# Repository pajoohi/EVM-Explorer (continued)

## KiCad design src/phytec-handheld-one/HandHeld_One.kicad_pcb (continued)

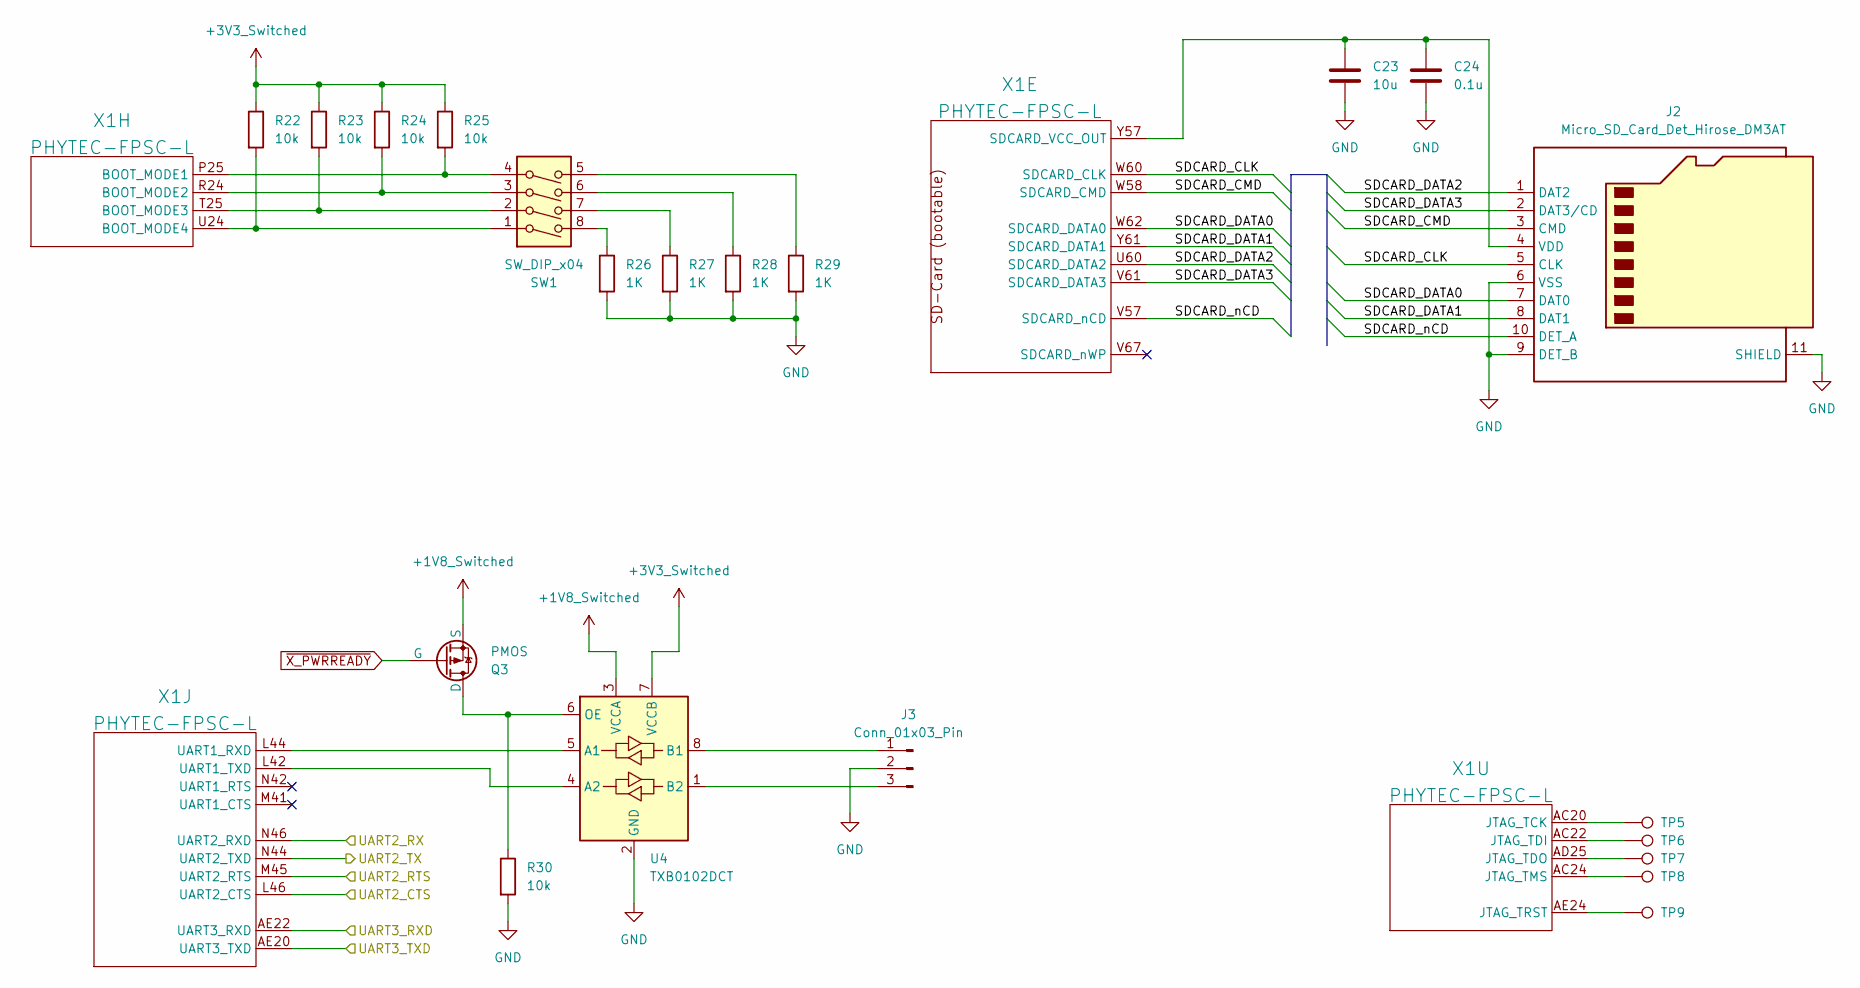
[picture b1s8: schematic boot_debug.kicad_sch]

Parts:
C23: 10u; C_0402_1005Metric_Pad0.74x0.62mm_HandSolder
C24: 0.1u; C_0402_1005Metric_Pad0.74x0.62mm_HandSolder
J2: Micro_SD_Card_Det_Hirose_DM3AT; microSD_HC_Hirose_DM3BT-DSF-PEJS
J3: Conn_01x03_Pin; PinHeader_1x03_P2.54mm_Vertical
Q3: PMOS; SC-59_Handsoldering
R22, R23, R24, R25, R30: 10k; R_0402_1005Metric_Pad0.72x0.64mm_HandSolder
R26, R27, R28, R29: 1K; R_0402_1005Metric_Pad0.72x0.64mm_HandSolder
SW1: SW_DIP_x04; SW_DIP_SPSTx04_Slide_Copal_CHS-04B_W7.62mm_P1.27mm
TP5, TP6, TP7, TP8, TP9: TestPoint; TestPoint_Pad_D1.0mm
U4: TXB0102DCT; TSSOP-8_3x3mm_P0.65mm
X1: PHYTEC-FPSC-L; PHYTEC-FPSC-BASIS-L-Socket

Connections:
+1V8_Switched: Q3.2 (S), U4.3 (VCCA); also elsewhere on the board
+3V3_Switched: R22.1, R23.1, R24.1, R25.1, U4.7 (VCCB); also elsewhere on the board
/Boot and Debug/SDCARD_CLK: J2.5 (CLK), X1.W60 (SDCARD_CLK)
/Boot and Debug/SDCARD_CMD: J2.3 (CMD), X1.W58 (SDCARD_CMD)
/Boot and Debug/SDCARD_DATA0: J2.7 (DAT0), X1.W62 (SDCARD_DATA0)
/Boot and Debug/SDCARD_DATA1: J2.8 (DAT1), X1.Y61 (SDCARD_DATA1)
/Boot and Debug/SDCARD_DATA2: J2.1 (DAT2), X1.U60 (SDCARD_DATA2)
/Boot and Debug/SDCARD_DATA3: J2.2 (DAT3/CD), X1.V61 (SDCARD_DATA3)
/Boot and Debug/SDCARD_nCD: J2.10 (DET_A), X1.V57 (SDCARD_nCD)
/Boot and Debug/UART2_CTS: X1.L46 (UART2_CTS); also elsewhere on the board
/Boot and Debug/UART2_RTS: X1.M45 (UART2_RTS); also elsewhere on the board
/Boot and Debug/UART2_RX: X1.N46 (UART2_RXD); also elsewhere on the board
/Boot and Debug/UART2_TX: X1.N44 (UART2_TXD); also elsewhere on the board
/Boot and Debug/UART3_RXD: X1.AE22 (UART3_RXD)
/Boot and Debug/UART3_TXD: X1.AE20 (UART3_TXD)
GND: C23.2, C24.2, J2.6 (VSS), J2.9 (DET_B), J2.11 (SHIELD), J3.2, R26.2, R27.2, R28.2, R29.2, R30.2, U4.2 (GND); also elsewhere on the board
unnamed: C23.1, C24.1, J2.4 (VDD), X1.Y57 (SDCARD_VCC_OUT)
unnamed: J3.1, U4.8 (B1)
unnamed: J3.3, U4.1 (B2)
unnamed: Q3.3 (D), R30.1, U4.6 (OE)
unnamed: R26.1, SW1.8
unnamed: R27.1, SW1.7
unnamed: R28.1, SW1.6
unnamed: R29.1, SW1.5
unnamed: U4.5 (A1), X1.L44 (UART1_RXD)
unnamed: U4.4 (A2), X1.L42 (UART1_TXD)
unnamed: R25.2, SW1.4, X1.P25 (BOOT_MODE1)
unnamed: R24.2, SW1.3, X1.R24 (BOOT_MODE2)
unnamed: R23.2, SW1.2, X1.T25 (BOOT_MODE3)
unnamed: R22.2, SW1.1, X1.U24 (BOOT_MODE4)
unnamed: TP5.1, X1.AC20 (JTAG_TCK)
unnamed: TP6.1, X1.AC22 (JTAG_TDI)
unnamed: TP7.1, X1.AD25 (JTAG_TDO)
unnamed: TP8.1, X1.AC24 (JTAG_TMS)
unnamed: TP9.1, X1.AE24 (JTAG_TRST)
~X_PWRREADY: Q3.1 (G); also elsewhere on the board

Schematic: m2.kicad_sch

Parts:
C51, C53: 1u; C_0402_1005Metric_Pad0.74x0.62mm_HandSolder
C52, C54: 0.1u; C_0402_1005Metric_Pad0.74x0.62mm_HandSolder
J6: Bus_M.2_Socket_E; JAE_SM3ZS067U310AER1200
MP1: M2 x 1.5mm; WA-SMSI_9774015243; PART-NUMBER 9774015243R
Q4: PMOS; SC-59_Handsoldering
X1: PHYTEC-FPSC-L; PHYTEC-FPSC-BASIS-L-Socket
XTAL1: OM-7604-C7-32.768KHZ-20PPM-TA-QC; OM-7604-C7_MCX

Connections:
+3V3_Switched: C51.1, C52.1, C53.1, C54.1, J6.2 (3.3V), J6.4 (3.3V), J6.72 (3.3V), J6.74 (3.3V), XTAL1.3 (CLKOE), XTAL1.4 (VDD); also elsewhere on the board
+5V: Q4.2 (S); also elsewhere on the board
/Boot and Debug/UART2_CTS: J6.34 (UART_CTS); also elsewhere on the board
/Boot and Debug/UART2_RTS: J6.36 (UART_RTS); also elsewhere on the board
/Boot and Debug/UART2_RX: J6.22 (UART_RXD); also elsewhere on the board
/Boot and Debug/UART2_TX: J6.32 (UART_TXD); also elsewhere on the board
/Display/TP_I2C_SCL: J6.60 (I2C_CLK); also elsewhere on the board
/Display/TP_I2C_SDA: J6.58 (I2C_DATA); also elsewhere on the board
/IO/GPIO1: J6.62 (~ALERT); also elsewhere on the board
/IO/GPIO4: J6.21 (~SDIO_WAKE); also elsewhere on the board
/M.2/USB2_D+: J6.3 (USB_D+), X1.AA62 (USB2_D_P)
/M.2/USB2_D-: J6.5 (USB_D-), X1.AB61 (USB2_D_N)
/M.2/~M.2_UART_Wake: J6.20 (~UART_WAKE)
GND: C51.2, C52.2, C53.2, C54.2, J6.1 (GND), J6.7 (GND), J6.18 (GND), J6.33 (GND), J6.39 (GND), J6.45 (GND), J6.51 (GND), J6.57 (GND), J6.63 (GND), J6.69 (GND), J6.75 (GND), J6.S1, J6.S2, MP1.1, XTAL1.2 (GND); also elsewhere on the board
unnamed: J6.9 (SDIO_CLK), X1.H57 (SDIO_CLK)
unnamed: J6.11 (SDIO_CMD), X1.G56 (SDIO_CMD)
unnamed: J6.13 (SDIO_DATA0), X1.G62 (SDIO_DATA0)
unnamed: J6.15 (SDIO_DATA1), X1.H61 (SDIO_DATA1)
unnamed: J6.17 (SDIO_DATA2), X1.G60 (SDIO_DATA2)
unnamed: J6.19 (SDIO_DATA3), X1.G58 (SDIO_DATA3)
unnamed: J6.50 (SUSCLK), XTAL1.1 (CLKOUT)
unnamed: Q4.3 (D), X1.AA58 (USB2_VBUS)
~X_PWRREADY: Q4.1 (G); also elsewhere on the board

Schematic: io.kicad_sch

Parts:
C49, C50: 0.1u; C_0402_1005Metric_Pad0.74x0.62mm_HandSolder
R39, R40, R41, R42, R43, R44: 2k; R_0402_1005Metric_Pad0.72x0.64mm_HandSolder
U8: ADXL343; LGA-14_3x5mm_P0.8mm_LayoutBorder1x6y
X1: PHYTEC-FPSC-L; PHYTEC-FPSC-BASIS-L-Socket

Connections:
+1V8_Switched: C50.1, R39.1, R40.1, R41.1, R42.1, R43.1, R44.1, U8.1 (Vdd_I/O); also elsewhere on the board
+3V3_Switched: C49.1, U8.6 (Vs); also elsewhere on the board
/Audio/Audio_I2C_SCL: R40.2, X1.L60 (I2C2_SCL); also elsewhere on the board
/Audio/Audio_I2C_SDA: R39.2, X1.L58 (I2C2_SDA); also elsewhere on the board
/Display/LCD_BKLT_PWM: X1.AN52 (PWM4); also elsewhere on the board
/Display/LCD_PWM: X1.AL42 (PWM3); also elsewhere on the board
/Display/TP_I2C_SCL: R42.2, X1.M61 (I2C3_SCL); also elsewhere on the board
/Display/TP_I2C_SDA: R41.2, X1.N60 (I2C3_SDA); also elsewhere on the board
/Display/TP_INT: X1.AL32 (GPIO3); also elsewhere on the board
/Display/TP_RST: X1.AN30 (GPIO5); also elsewhere on the board
/IO/GPIO1: X1.N40 (GPIO1); also elsewhere on the board
/IO/GPIO4: X1.AL34 (GPIO4); also elsewhere on the board
/IO/GPIO6: X1.AN32 (GPIO6); also elsewhere on the board
/IO/GPIO7: X1.AN34 (GPIO7); also elsewhere on the board
/IO/I2C4_SCL: R44.2, X1.AN40 (I2C5_SCL/I3C_SCL); also elsewhere on the board
/IO/I2C4_SDA: R43.2, X1.AN42 (I2C5_SDA/I3C_SDA); also elsewhere on the board
/IO/SPI1.MISO: U8.12 (SDO/ADDR), X1.N34 (SPI1_MISO)
/IO/SPI1.MOSI: U8.13 (SDA/SDI/SDIO), X1.N32 (SPI1_MOSI)
/IO/SPI1.SCLK: U8.14 (SCL/SCLK), X1.M33 (SPI1_SCLK)
/IO/SPI1.~CS: U8.7 (~CS), X1.L34 (SPI1_nCS)
GND: C49.2, C50.2, U8.2 (GND), U8.4 (GND), U8.5 (GND); also elsewhere on the board
unnamed: U8.8 (INT1), X1.L40 (GPIO2)

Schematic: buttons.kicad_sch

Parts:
R47: 10k; R_0402_1005Metric_Pad0.72x0.64mm_HandSolder
SW2: SW_Push; SW_EVP-ASAC1A

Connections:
+1V8_Switched: R47.1; also elsewhere on the board
/Micro Controller/Button/button: R47.2, SW2.1; also elsewhere on the board
GND: SW2.2; also elsewhere on the board

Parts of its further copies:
R48, R49, R50, R51, R52, R53, R54, R55, R56, R57: 10k; R_0402_1005Metric_Pad0.72x0.64mm_HandSolder
SW3, SW4, SW5, SW6, SW7, SW8, SW9, SW10, SW11, SW12: SW_Push; SW_EVP-ASAC1A

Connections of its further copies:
+1V8_Switched: R48.1, R49.1, R50.1, R51.1, R52.1, R53.1, R54.1, R55.1, R56.1, R57.1; also elsewhere on the board
/Micro Controller/Button1/button: R48.2, SW3.1; also elsewhere on the board
/Micro Controller/Button2/button: R49.2, SW4.1; also elsewhere on the board
/Micro Controller/Button3/button: R50.2, SW5.1; also elsewhere on the board
/Micro Controller/Button4/button: R51.2, SW6.1; also elsewhere on the board
/Micro Controller/Button5/button: R52.2, SW7.1; also elsewhere on the board
/Micro Controller/Button6/button: R53.2, SW8.1; also elsewhere on the board
/Micro Controller/Button7/button: R54.2, SW9.1; also elsewhere on the board
/Micro Controller/Button8/button: R55.2, SW10.1; also elsewhere on the board
/Micro Controller/Button9/button: R56.2, SW11.1; also elsewhere on the board
/Micro Controller/Button10/button: R57.2, SW12.1; also elsewhere on the board
GND: SW3.2, SW4.2, SW5.2, SW6.2, SW7.2, SW8.2, SW9.2, SW10.2, SW11.2, SW12.2; also elsewhere on the board

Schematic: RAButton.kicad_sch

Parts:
R60: 10k; R_0402_1005Metric_Pad0.72x0.64mm_HandSolder
SW15: SW_Push_Shielded; SW_EVQ-P46B3M

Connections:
+1V8_Switched: R60.1; also elsewhere on the board
/Micro Controller/Right Angle Button1/button: R60.2, SW15.1; also elsewhere on the board
GND: SW15.2, SW15.3 (B), SW15.4 (B); also elsewhere on the board

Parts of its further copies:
R58: 10k; R_0402_1005Metric_Pad0.72x0.64mm_HandSolder
SW13: SW_Push_Shielded; SW_EVQ-P46B3M

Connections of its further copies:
+1V8_Switched: R58.1; also elsewhere on the board
/Micro Controller/Right Angle Button/button: R58.2, SW13.1; also elsewhere on the board
GND: SW13.2, SW13.3 (B), SW13.4 (B); also elsewhere on the board

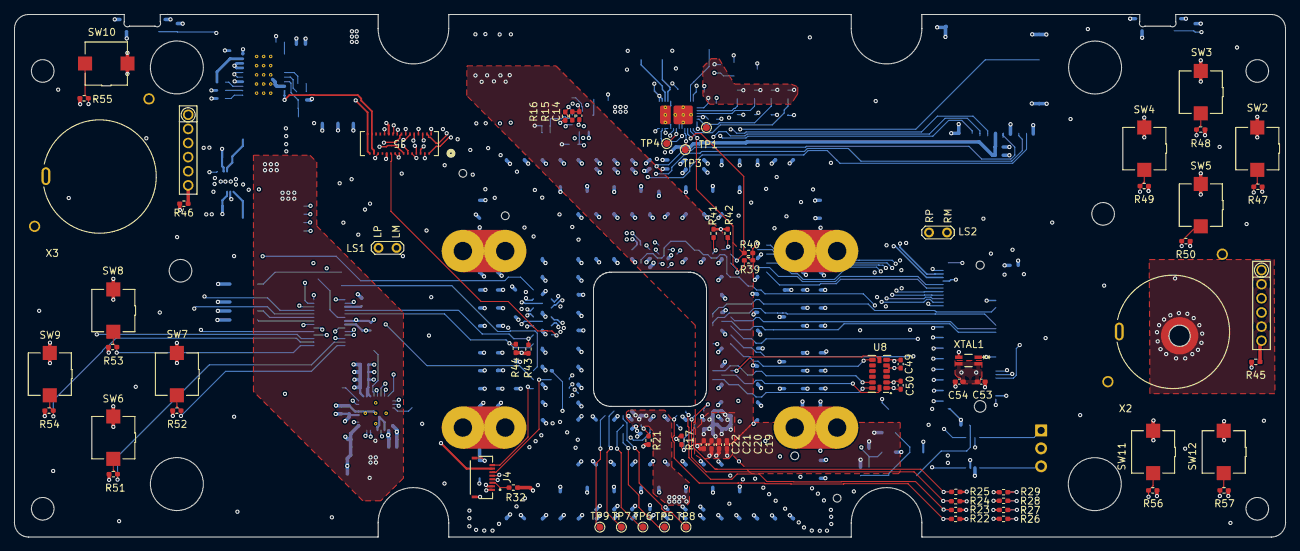
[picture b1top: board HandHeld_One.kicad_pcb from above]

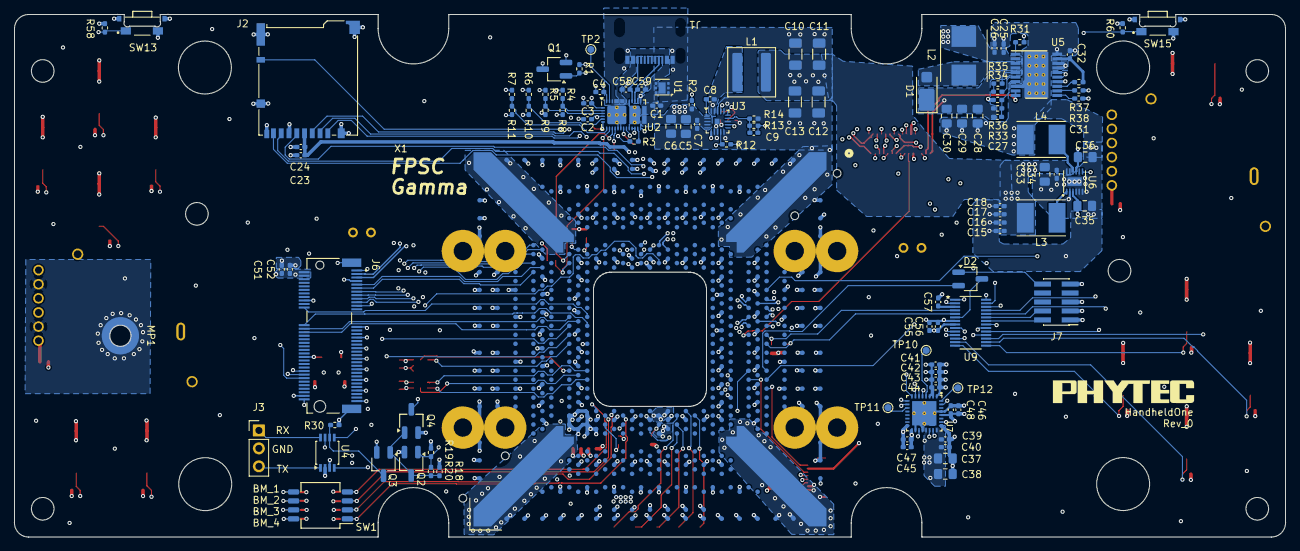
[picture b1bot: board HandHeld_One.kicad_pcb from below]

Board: 6 copper layers, 180.0 x 74.0 mm, 177 parts (109 on the bottom side), 154 nets.

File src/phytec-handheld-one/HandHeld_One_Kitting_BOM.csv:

Reference,Qty,Value / Size ,DNP
C1,1,4.7u 0402,
"C2,C3,C4,C23,C25,C26,C41,C42,C45,C46,C55",11,10u 0402,
"C5,C6,C33,C35,C36,C37,C38",7,22u 0805,
"C7,C8,C15,C16,C17,C18,C19,C20,C21,C22,C24,C34,C39,C40,C43,C44,C47,C48,C49,C50,C52,C54,C56",23,0.1u 0402,
C9,1,47p 0402,
"C10,C11,C12,C13",4,47u 1206,
"C14,C31,C32,C51,C53",5,1u 0402,
C27,1,10p 0402,
"C28,C29",2,2.2u 0805,
C30,1,1u 0805,
C57,1,470n 0402,
"C58,C59",2,330p 0402,
D1,1,D_Shockley,
D2,1,D_Dual_CommonAnode_KKA_Parallel,
J1,1,USB_C_Receptacle_USB2.0_14P,
J2,1,Micro_SD_Card_Det_Hirose_DM3AT,
J3,1,Conn_01x03_Pin 2.54mm,
J4,1,2328702-8,
J5,1,AYF333135,
J6,1,Bus_M.2_Socket_E PHYTEC:JAE_SM3ZS067U310AER1200,
J7,1,Conn_ARM_JTAG_SWD_10 PinHeader 2x05_P1.27mm,
L1,1,4.7u L_Coilcraft_XAL6060-XXX,
L2,1,15u IND_AMPLA7030Q-150MT,
"L3,L4",2,4.7u L_Taiyo-Yuden_NR-50xx,
"LS1,LS2",2,Speaker 2Pads_Pitch2.54mm,
MP1,1,M2 x 1.5mm WA-SMSI_9774015243,
"Q1,Q2",2,Q_NMOS_GSD SC-59,
"Q3,Q4",2,PMOS SC-59,
"R1,R2,R3,R12,R17,R18,R19,R21,R22,R23,R24,R25,R30,R31,R47,R48,R49,R50,R51,R52,R53,R54,R55,R56,R57,R58,R60",27,10k 0402,
"R4,R5,R6,R7",4,100k 0402,
"R8,R10,R16",3,5.1k 0402,
R9,1,R 0402,DNP
R11,1,23.2k 0402,
"R13,R34",2,220k 0402,
R14,1,30k 0402,
R15,1,330k 0402,
R20,1,0R 0402,DNP
"R26,R27,R28,R29",4,1K 0402,
"R32,R45,R46",3,0R 0402,
R33,1,360k 0402,
"R35,R37",2,47k 0402,
R36,1,20k 0402,
R38,1,15k 0402,
"R39,R40,R41,R42,R43,R44",6,2k 0402,
SW1,1,SW_DIP_x04 CHS-04B_W7.62mm_P1.27mm,
"SW2,SW3,SW4,SW5,SW6,SW7,SW8,SW9,SW10,SW11,SW12",11,SW_Push SW_EVP-ASAC1A,
"SW13,SW15",2,SW_Push_Shielded SW_EVQ-P46B3M,
"TP1,TP2,TP3,TP4,TP5,TP6,TP7,TP8,TP9,TP10,TP11,TP12",12,TestPoint,
U1,1,TVS2200DRV WSON-6-1EP_2x2mm_P0.65mm_EP1x1.6mm,
U2,1,TPS25730D  Texas_REF0038A_WQFN-38-2EP_6x4mm_P0.4,
U3,1,TPS51396A  Texas_RJE0020A_VQFN-20-1EP_3x3mm_P0.45mm,
U4,1,TXB0102DCT  TSSOP-8_3x3mm_P0.65mm,
U5,1,LM3492MHX/NOPB   PWP0020A_N,
U6,1,TPS65133DPDR  SON40P300X300X80-13N,
U7,1,TLV320AIC3110IRHBR  IC_ADS125H01IRHBT,
U8,1,ADXL343  LGA-14_3x5mm_P0.8mm,
U9,1,MSPM0L1306xDGS28,
X1,1,PHYTEC-FPSC-L  PHYTEC-FPSC-BASIS-L-Socket,
"X2,X3",2,5628 Joystick Switches -  Adafruit Industries,
XTAL1,1,OM-7604-C7-32.768KHZ-20PPM-TA-QC,

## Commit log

2026-03-15 chore: cleanup boilerplate, UI polish and setup gh-pages
2026-04-21 Fix Board Versions
2026-04-21 Fix Image Loading and Design Files examples for AM62P
2026-04-21 Add Red Lettering for S, K and AM
2026-04-21 Add Deploy
2026-06-08 Add PHYTEC Handheld One platform source configuration
2026-06-10 Refactor: Move entry to public/evms and structure design assets
